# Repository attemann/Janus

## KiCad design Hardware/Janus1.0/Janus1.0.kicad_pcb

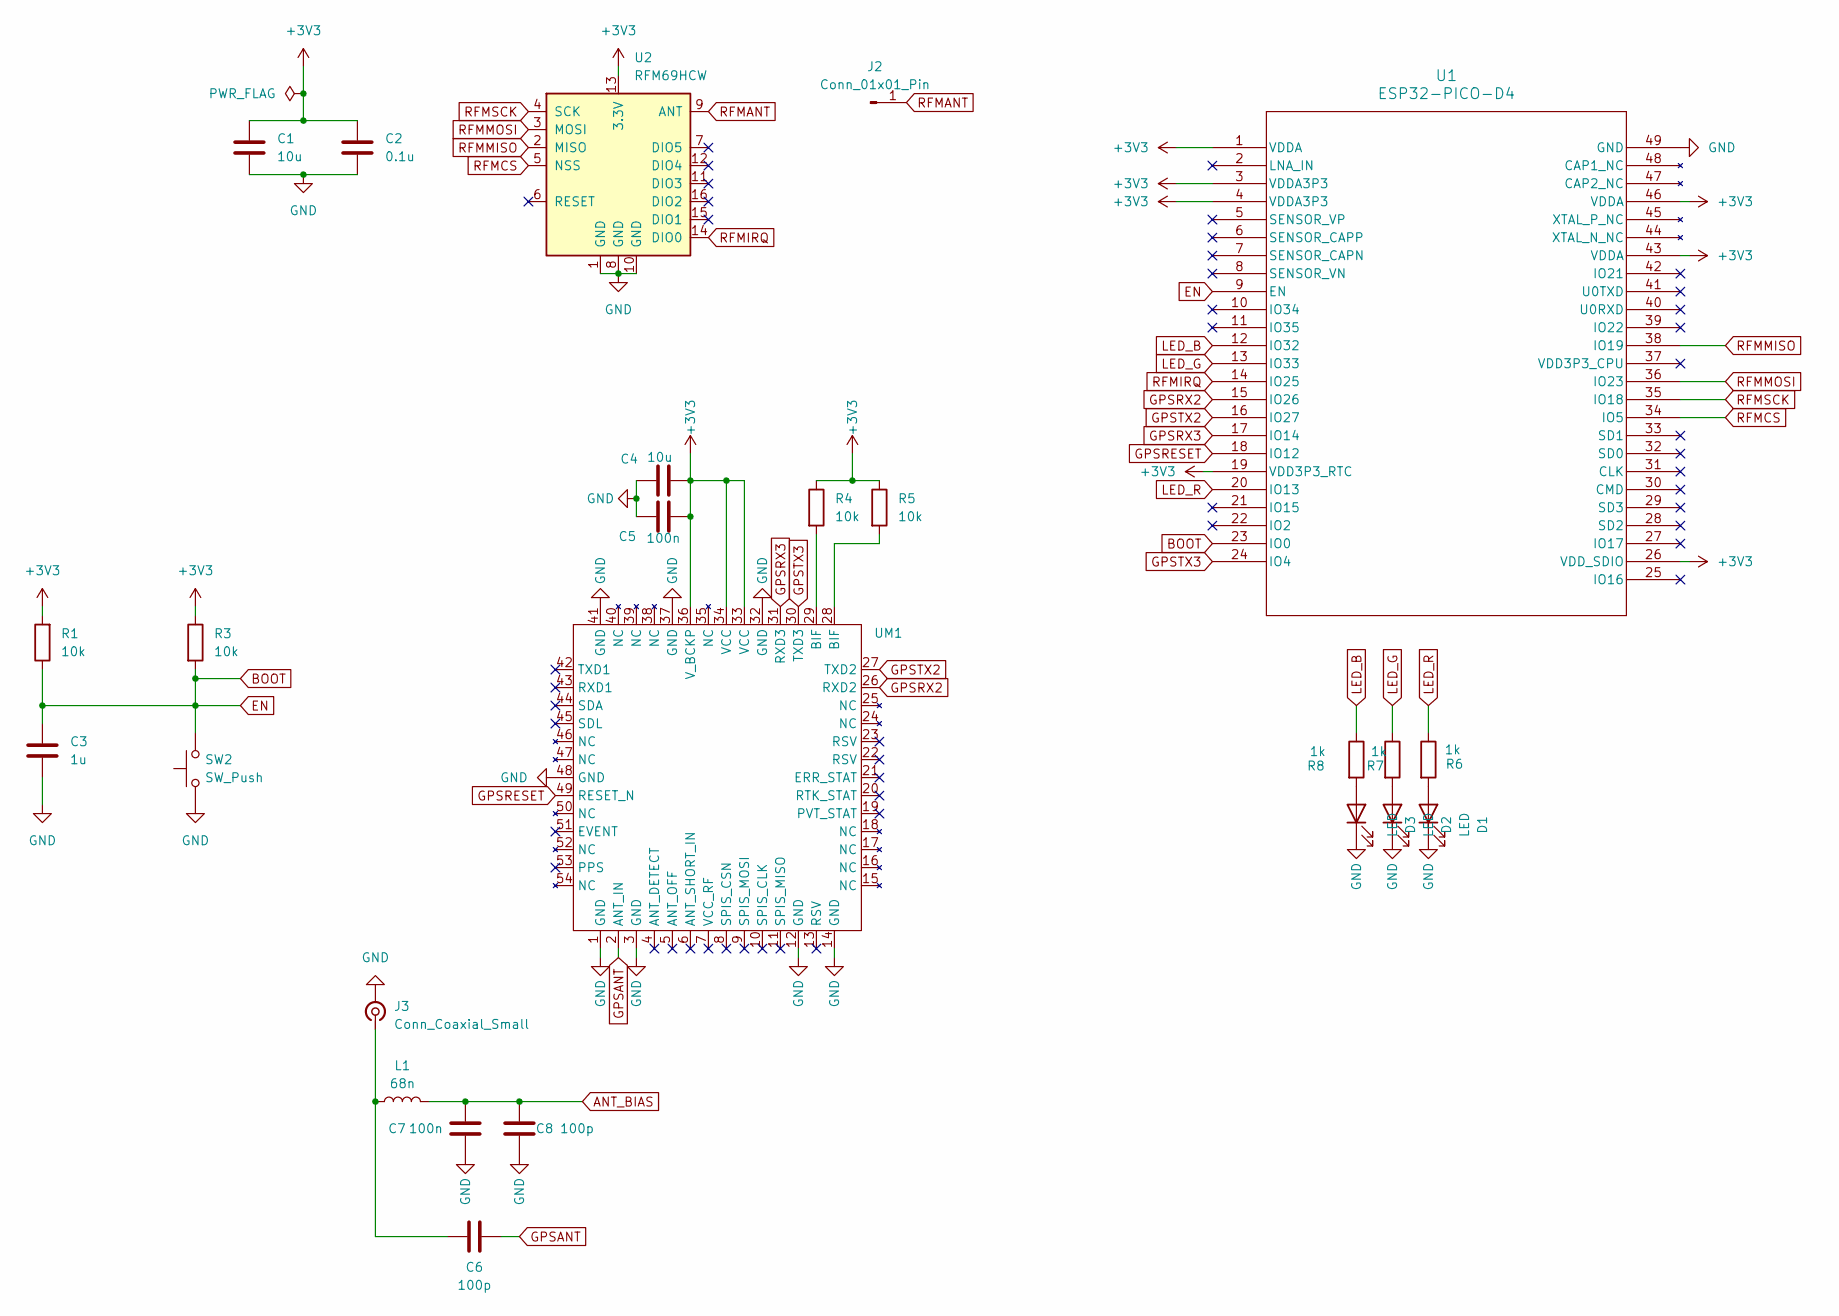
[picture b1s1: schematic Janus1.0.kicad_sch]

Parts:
C1, C4: 10u; C_0201_0603Metric
C2: 0.1u; C_0201_0603Metric
C3: 1u; C_0201_0603Metric
C5, C7: 100n; C_0201_0603Metric
C6, C8: 100p; C_0201_0603Metric
D1, D2, D3: LED; LED_0603_1608Metric
J2: Conn_01x01_Pin; PinHeader_1x01_P2.54mm_Vertical
J3: Conn_Coaxial_Small; U.FL_Hirose_U.FL-R-SMT-1_Vertical
L1: 68n; L_0201_0603Metric
R1, R3, R4, R5: 10k; R_0201_0603Metric
R6, R7, R8: 1k; R_0201_0603Metric
SW2: SW_Push; SW_Push_1P1T_NO_CK_PTS125Sx43PSMTR
U1: ESP32-PICO-D4; ESP32-PICO-D4_EXP
U2: RFM69HCW; MOD_COM-13909
UM1: UM980

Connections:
+3V3: C1.1, C2.1, C4.1, C5.1, R1.2, R3.1, R4.1, R5.1, U1.1 (VDDA), U1.3 (VDDA3P3), U1.4 (VDDA3P3), U1.19 (VDD3P3_RTC), U1.26 (VDD_SDIO), U1.43 (VDDA), U1.46 (VDDA), U2.13 (3.3V), UM1.33 (VCC), UM1.34 (VCC), UM1.36 (V_BCKP)
ANT_BIAS: C7.2, C8.2, L1.2
BOOT: C3.1, R1.1, R3.2, SW2.2, U1.9 (EN), U1.23 (IO0)
GND: C1.2, C2.2, C3.2, C4.2, C5.2, C7.1, C8.1, D1.1 (K), D2.1 (K), D3.1 (K), J3.2 (Ext), SW2.1, U1.49 (GND), U2.1 (GND), U2.8 (GND), U2.10 (GND), UM1.1 (GND), UM1.3 (GND), UM1.12 (GND), UM1.14 (GND), UM1.32 (GND), UM1.37 (GND), UM1.41 (GND), UM1.48 (GND)
GPSANT: C6.2, UM1.2 (ANT_IN)
GPSRESET: U1.18 (IO12), UM1.49 (RESET_N)
GPSRX2: U1.15 (IO26), UM1.26 (RXD2)
GPSRX3: U1.17 (IO14), UM1.31 (RXD3)
GPSTX2: U1.16 (IO27), UM1.27 (TXD2)
GPSTX3: U1.24 (IO4), UM1.30 (TXD3)
LED_B: R8.1, U1.12 (IO32)
LED_G: R7.1, U1.13 (IO33)
LED_R: R6.1, U1.20 (IO13)
unnamed: D1.2 (A), R6.2
unnamed: D2.2 (A), R7.2
unnamed: D3.2 (A), R8.2
unnamed: C6.1, J3.1 (In), L1.1
unnamed: R4.2, UM1.29 (BIF)
unnamed: R5.2, UM1.28 (BIF)
RFMANT: J2.1, U2.9 (ANT)
RFMCS: U1.34 (IO5), U2.5 (NSS)
RFMIRQ: U1.14 (IO25), U2.14 (DIO0)
RFMMISO: U1.38 (IO19), U2.2 (MISO)
RFMMOSI: U1.36 (IO23), U2.3 (MOSI)
RFMSCK: U1.35 (IO18), U2.4 (SCK)

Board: 4 copper layers, 25 parts (0 on the bottom side), 25 nets, no tracks yet.

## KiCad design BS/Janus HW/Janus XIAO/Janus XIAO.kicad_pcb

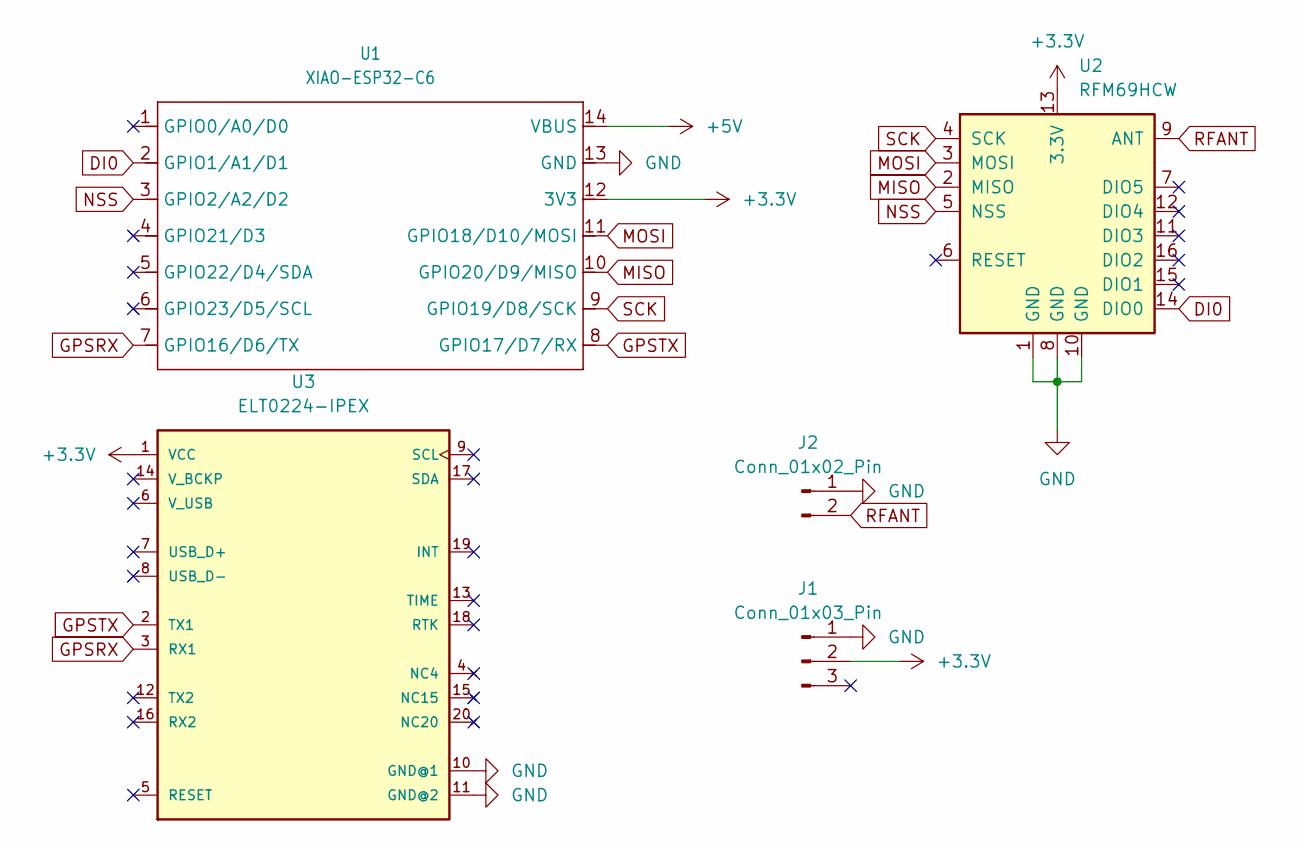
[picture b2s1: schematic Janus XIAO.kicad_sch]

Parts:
J1: Conn_01x03_Pin; PinHeader_1x03_P2.54mm_Vertical
J2: Conn_01x02_Pin; PinHeader_1x02_P2.54mm_Vertical
U1: XIAO-ESP32-C6; MCU_Seeed_ESP32C6 joe
U2: RFM69HCW; HOPERF_RFM9XW_SMD
U3: ELT0224-IPEX

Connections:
+3.3V: J1.2, U1.12 (3V3), U2.13 (3.3V), U3.1 (VCC)
+5V: U1.14 (VBUS)
DI0: U1.2 (GPIO1/A1/D1), U2.14 (DIO0)
GND: J1.1, J2.1, U1.13 (GND), U2.1 (GND), U2.8 (GND), U2.10 (GND), U3.10 (GND@1), U3.11 (GND@2)
GPSRX: U1.7 (GPIO16/D6/TX), U3.3 (RX1)
GPSTX: U1.8 (GPIO17/D7/RX), U3.2 (TX1)
MISO: U1.10 (GPIO20/D9/MISO), U2.2 (MISO)
MOSI: U1.11 (GPIO18/D10/MOSI), U2.3 (MOSI)
NSS: U1.3 (GPIO2/A2/D2), U2.5 (NSS)
RFANT: J2.2, U2.9 (ANT)
SCK: U1.9 (GPIO19/D8/SCK), U2.4 (SCK)

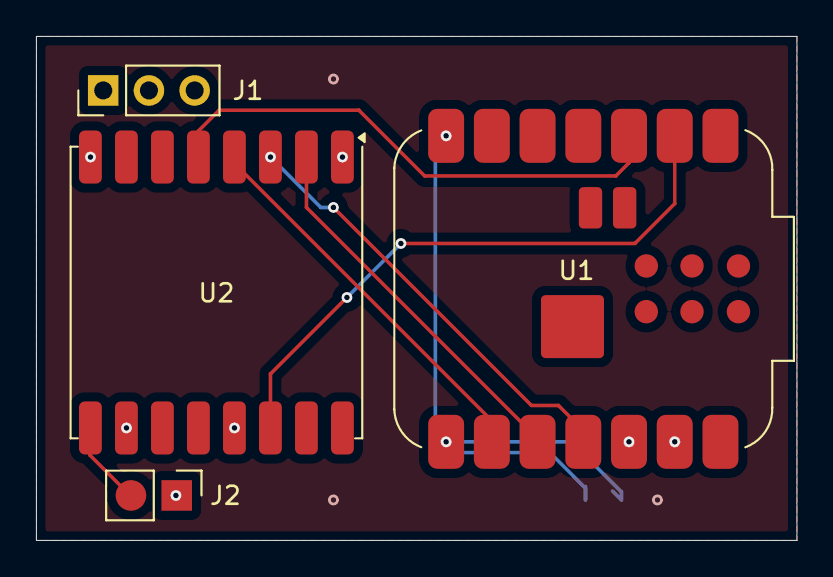
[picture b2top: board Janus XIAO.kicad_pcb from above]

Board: 4 copper layers, 42.2 x 28.0 mm, 5 parts (1 on the bottom side), 10 nets.

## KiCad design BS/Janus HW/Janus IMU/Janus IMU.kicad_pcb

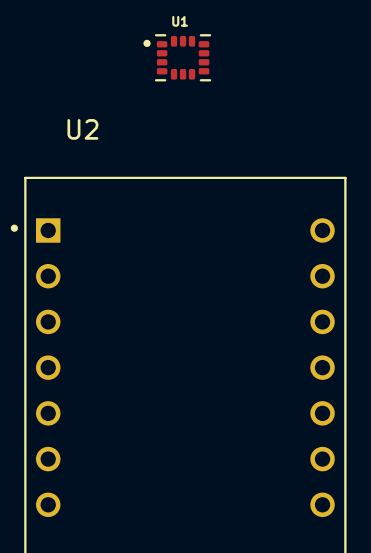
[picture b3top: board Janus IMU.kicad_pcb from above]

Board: 2 copper layers, 3 parts (1 on the bottom side), 3 nets, no tracks yet.

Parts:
U1: ICM-42688-P; PQFN50P300X250X97-14N
U2: XIAO ESP32-C6; MODULE_113991054
U4: RFM69HCW; HOPERF_RFM9XW_SMD

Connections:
+3.3V: U1.8 (VDD), U2.12 (VCC_3V3), U4.13 (3.3V)
GND: U1.6 (GND), U2.13 (GND), U4.1 (GND), U4.8 (GND), U4.10 (GND)
SCK: U4.2 (MISO), U4.3 (MOSI), U4.4 (SCK), U4.5 (NSS), U4.14 (DIO0)

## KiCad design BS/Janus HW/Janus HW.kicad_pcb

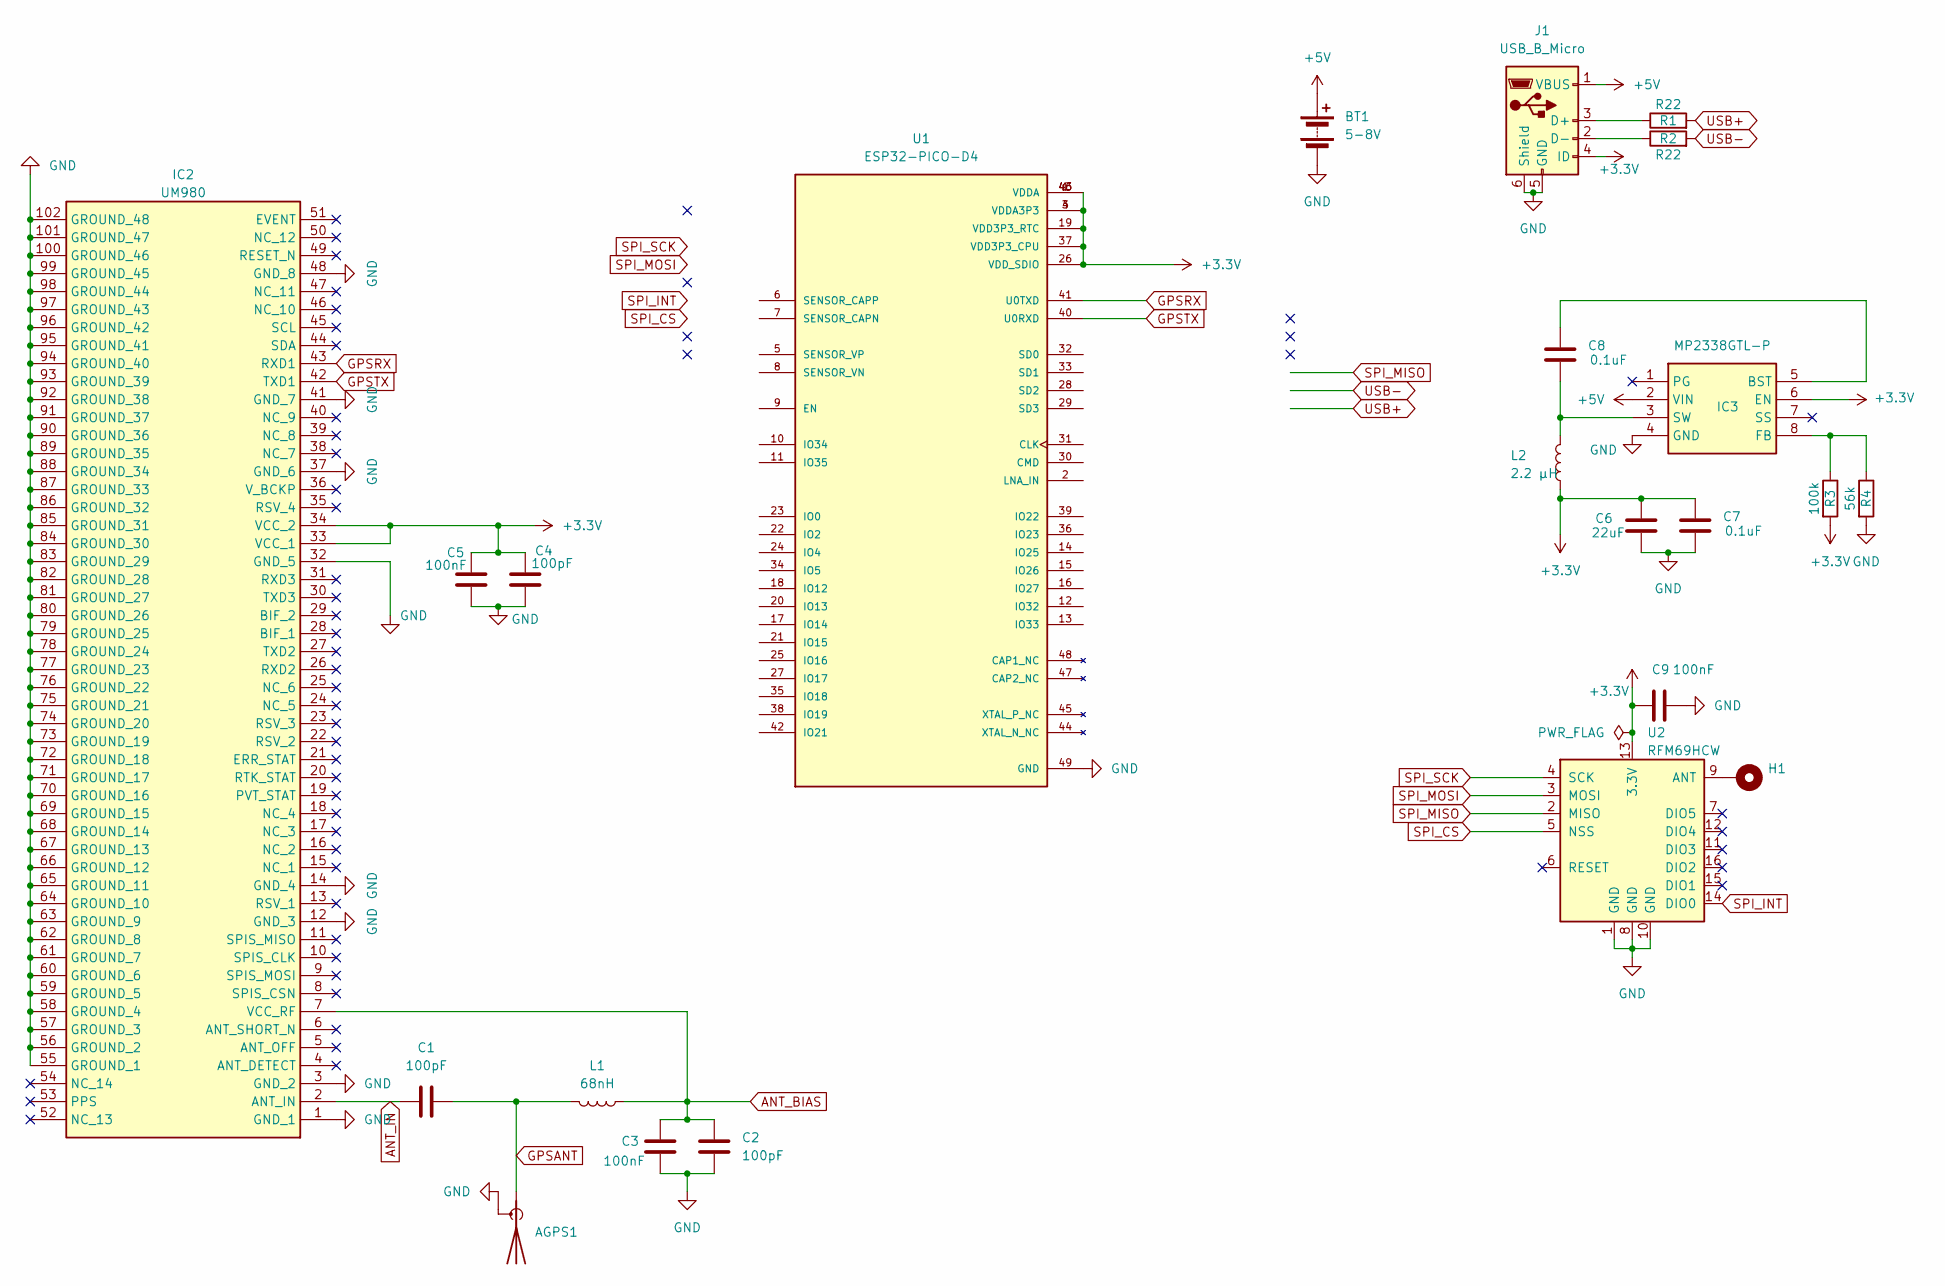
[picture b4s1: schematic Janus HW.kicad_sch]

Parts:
AGPS1: Antenna_Shield; U.FL_Molex_MCRF_73412-0110_Vertical
BT1: 5-8V
C1, C2, C4: 100pF; C_0201_0603Metric_Pad0.64x0.40mm_HandSolder
C3, C5, C9: 100nF; C_0201_0603Metric_Pad0.64x0.40mm_HandSolder
C6: 22uF; C_0201_0603Metric_Pad0.64x0.40mm_HandSolder
C7, C8: 0.1uF; C_0201_0603Metric_Pad0.64x0.40mm_HandSolder
H1: MountingHole_Pad; PinHeader_1x01_P1.27mm_Vertical
IC2: UM980; Manufacturer_Part_Number UM980
IC3: MP2338GTL-P; SOTFL50P160X60-8N; Manufacturer_Part_Number MP2338GTL-P; Mouser Part Number 946-MP2338GTL-P
J1: USB_B_Micro; USB_Micro-B_Amphenol_10118194-0001LF_Horizontal
L1: 68nH; L_0201_0603Metric
L2: 2.2 µH; L_0805_2012Metric
R1, R2: R22; R_0201_0603Metric_Pad0.64x0.40mm_HandSolder
R3: 100k; R_0201_0603Metric_Pad0.64x0.40mm_HandSolder
R4: 56k; R_0201_0603Metric_Pad0.64x0.40mm_HandSolder
U1: ESP32-PICO-D4; QFN-48-1EP_6x6mm_P0.4mm_EP4.3x4.3mm_ThermalVias; PARTREV v1.9; DigiKey_Part_Number 1904-1029-2-ND
U2: RFM69HCW; HOPERF_RFM9XW_THT_ikke_through

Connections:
+3.3V: C4.2, C5.2, C6.2, C7.2, C9.2, IC2.33 (VCC_1), IC2.34 (VCC_2), IC3.6 (EN), J1.4 (ID), L2.1, R3.2, U1.1 (VDDA), U1.3 (VDDA3P3), U1.4 (VDDA3P3), U1.19 (VDD3P3_RTC), U1.26 (VDD_SDIO), U1.37 (VDD3P3_CPU), U1.43 (VDDA), U1.46 (VDDA), U2.13 (3.3V)
+5V: BT1.1 (+), IC3.2 (VIN), J1.1 (VBUS)
ANT_BIAS: C2.2, C3.2, IC2.7 (VCC_RF), L1.1
ANT_IN: C1.1, IC2.2 (ANT_IN)
GND: AGPS1.2 (Shield), BT1.2 (-), C2.1, C3.1, C4.1, C5.1, C6.1, C7.1, C9.1, IC2.1 (GND_1), IC2.3 (GND_2), IC2.12 (GND_3), IC2.14 (GND_4), IC2.32 (GND_5), IC2.37 (GND_6), IC2.41 (GND_7), IC2.48 (GND_8), IC2.55 (GROUND_1), IC2.56 (GROUND_2), IC2.57 (GROUND_3), IC2.58 (GROUND_4), IC2.59 (GROUND_5), IC2.60 (GROUND_6), IC2.61 (GROUND_7), IC2.62 (GROUND_8), IC2.63 (GROUND_9), IC2.64 (GROUND_10), IC2.65 (GROUND_11), IC2.66 (GROUND_12), IC2.67 (GROUND_13), IC2.68 (GROUND_14), IC2.69 (GROUND_15), IC2.70 (GROUND_16), IC2.71 (GROUND_17), IC2.72 (GROUND_18), IC2.73 (GROUND_19), IC2.74 (GROUND_20), IC2.75 (GROUND_21), IC2.76 (GROUND_22), IC2.77 (GROUND_23), IC2.78 (GROUND_24), IC2.79 (GROUND_25), IC2.80 (GROUND_26), IC2.81 (GROUND_27), IC2.82 (GROUND_28), IC2.83 (GROUND_29), IC2.84 (GROUND_30), IC2.85 (GROUND_31), IC2.86 (GROUND_32), IC2.87 (GROUND_33), IC2.88 (GROUND_34), IC2.89 (GROUND_35), IC2.90 (GROUND_36), IC2.91 (GROUND_37), IC2.92 (GROUND_38), IC2.93 (GROUND_39), IC2.94 (GROUND_40), IC2.95 (GROUND_41), IC2.96 (GROUND_42), IC2.97 (GROUND_43), IC2.98 (GROUND_44), IC2.99 (GROUND_45), IC2.100 (GROUND_46), IC2.101 (GROUND_47), IC2.102 (GROUND_48), IC3.4 (GND), J1.5 (GND), J1.6 (Shield), R4.2, U1.49 (GND), U2.1 (GND), U2.8 (GND), U2.10 (GND)
GPSANT: AGPS1.1 (A), C1.2, L1.2
GPSRX: IC2.43 (RXD1), U1.41 (U0TXD)
GPSTX: IC2.42 (TXD1), U1.40 (U0RXD)
unnamed: C8.2, IC3.5 (BST)
unnamed: IC3.8 (FB), R3.1, R4.1
unnamed: C8.1, IC3.3 (SW), L2.2
unnamed: J1.3 (D+), R1.1
unnamed: J1.2 (D-), R2.1
unnamed: H1.1, U2.9 (ANT)
SPI_CS: U2.5 (NSS)
SPI_INT: U2.14 (DIO0)
SPI_MISO: U2.2 (MISO)
SPI_MOSI: U2.3 (MOSI)
SPI_SCK: U2.4 (SCK)
USB+: R1.2
USB-: R2.2

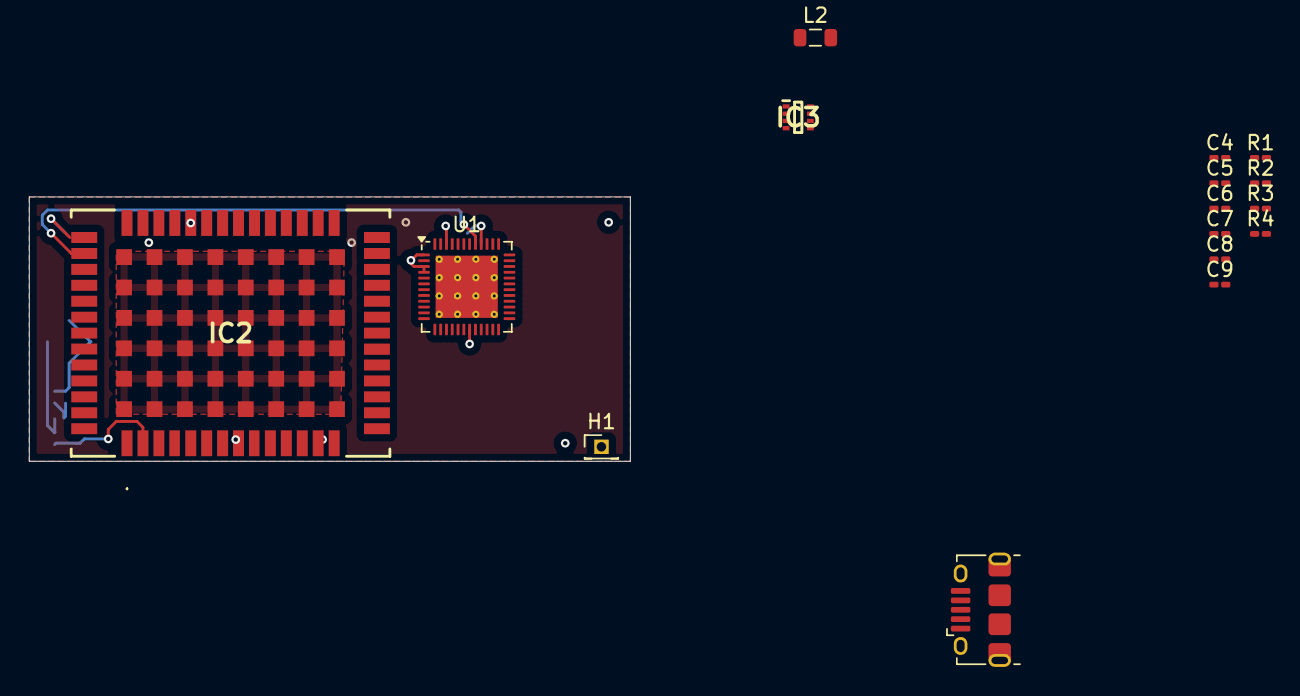
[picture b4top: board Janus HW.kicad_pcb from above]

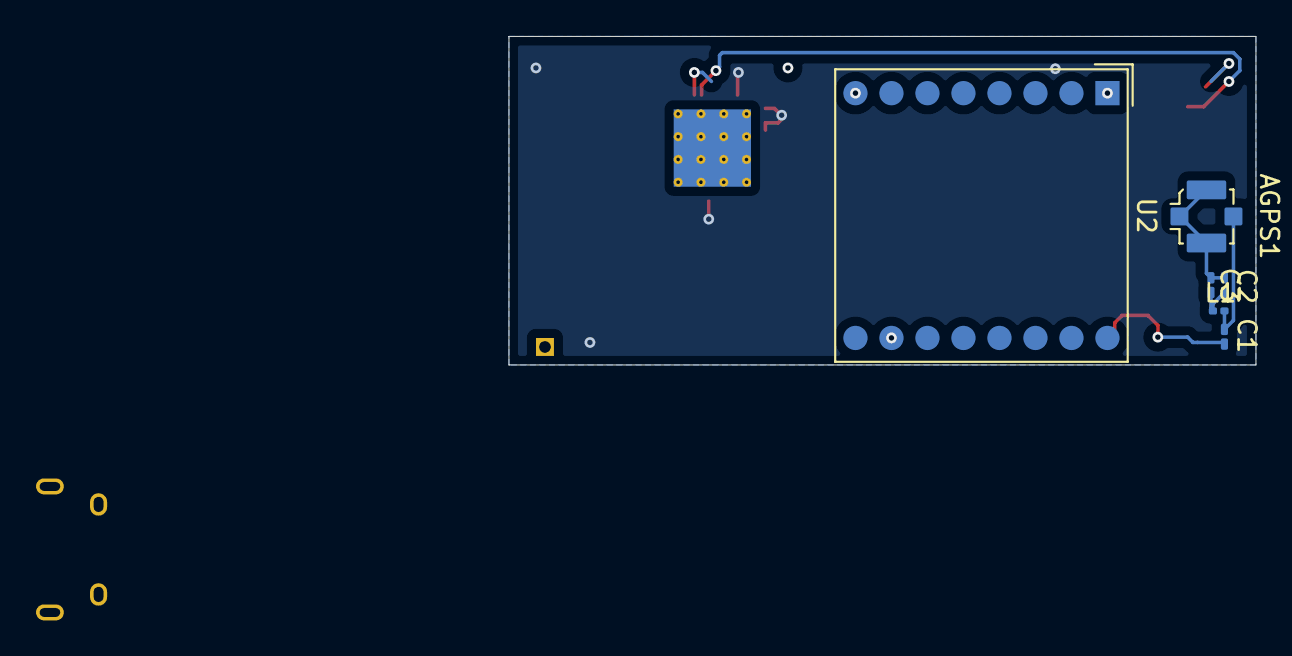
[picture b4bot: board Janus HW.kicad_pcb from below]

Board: 4 copper layers, 41.5 x 18.2 mm, 22 parts (6 on the bottom side), 14 nets.

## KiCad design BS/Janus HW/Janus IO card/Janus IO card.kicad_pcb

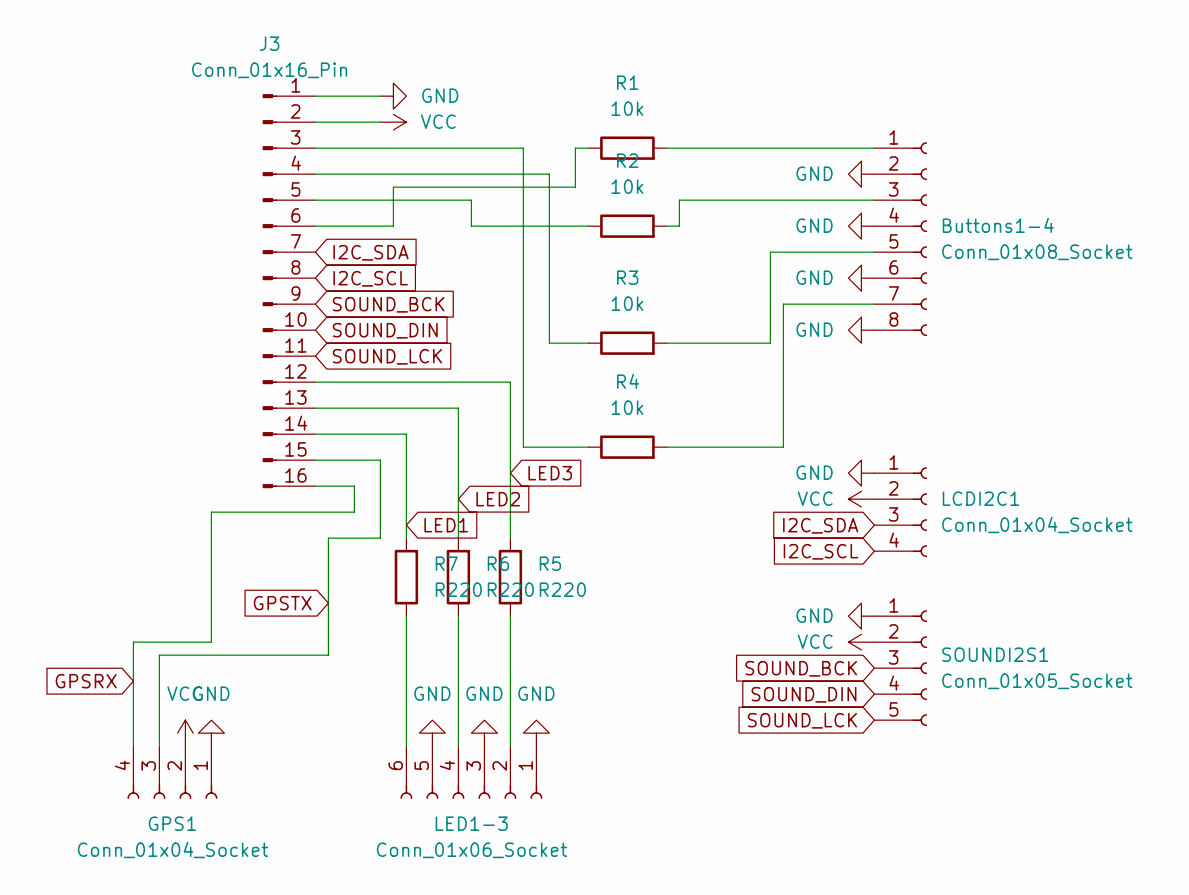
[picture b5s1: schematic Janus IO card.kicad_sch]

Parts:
Buttons1-4: Conn_01x08_Socket; JST_ZH_B8B-ZR_1x08_P1.50mm_Vertical
GPS1: Conn_01x04_Socket; JST_ZH_B4B-ZR_1x04_P1.50mm_Vertical
J3: Conn_01x16_Pin; TE_1-84952-6_1x16-1MP_P1.0mm_Horizontal
LCDI2C1: Conn_01x04_Socket; JST_ZH_B4B-ZR_1x04_P1.50mm_Vertical
LED1-3: Conn_01x06_Socket; JST_ZH_B6B-ZR_1x06_P1.50mm_Vertical
R1, R2, R3, R4: 10k; R_0805_2012Metric
R5, R6, R7: R220; R_0805_2012Metric
SOUNDI2S1: Conn_01x05_Socket; JST_ZH_B5B-ZR_1x05_P1.50mm_Vertical

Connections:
GND: Buttons1-4.2, Buttons1-4.4, Buttons1-4.6, Buttons1-4.8, GPS1.1, J3.1, LCDI2C1.1, LED1-3.1, LED1-3.3, LED1-3.5, SOUNDI2S1.1
GPSRX: GPS1.4, J3.16
GPSTX: GPS1.3, J3.15
I2C_SCL: J3.8, LCDI2C1.4
I2C_SDA: J3.7, LCDI2C1.3
LED1: J3.14, R7.2
LED2: J3.13, R6.2
LED3: J3.12, R5.2
unnamed: Buttons1-4.1, R1.2
unnamed: Buttons1-4.3, R2.2
unnamed: Buttons1-4.5, R3.2
unnamed: Buttons1-4.7, R4.2
unnamed: J3.3, R4.1
unnamed: J3.4, R3.1
unnamed: J3.5, R2.1
unnamed: J3.6, R1.1
unnamed: LED1-3.2, R5.1
unnamed: LED1-3.4, R6.1
unnamed: LED1-3.6, R7.1
SOUND_BCK: J3.9, SOUNDI2S1.3
SOUND_DIN: J3.10, SOUNDI2S1.4
SOUND_LCK: J3.11, SOUNDI2S1.5
VCC: GPS1.2, J3.2, LCDI2C1.2, SOUNDI2S1.2

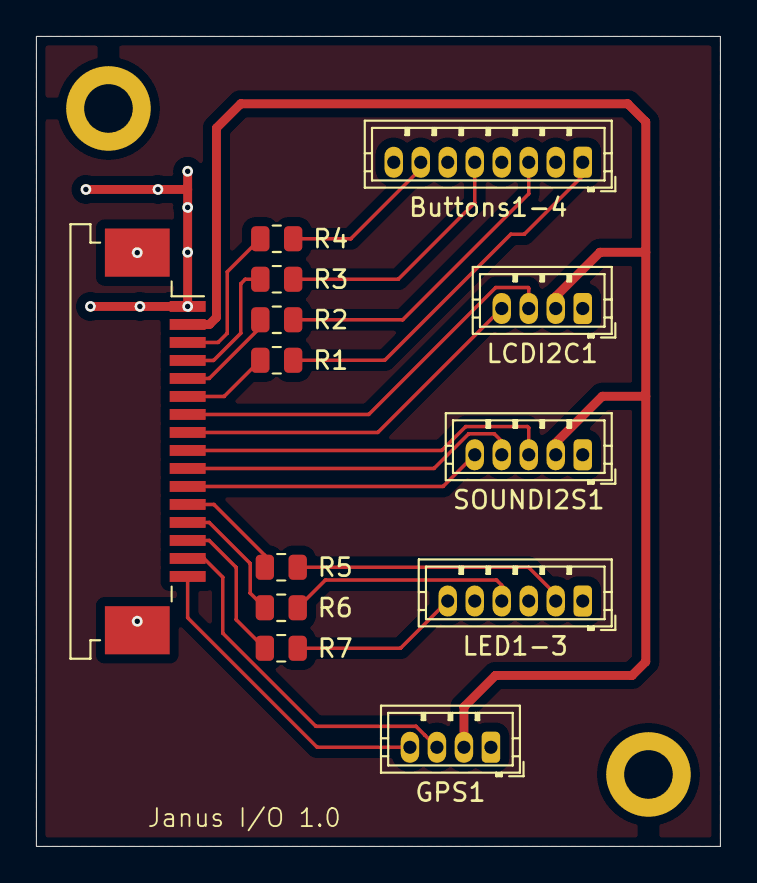
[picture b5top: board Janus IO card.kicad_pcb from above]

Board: 2 copper layers, 38.0 x 45.0 mm, 13 parts (0 on the bottom side), 23 nets.

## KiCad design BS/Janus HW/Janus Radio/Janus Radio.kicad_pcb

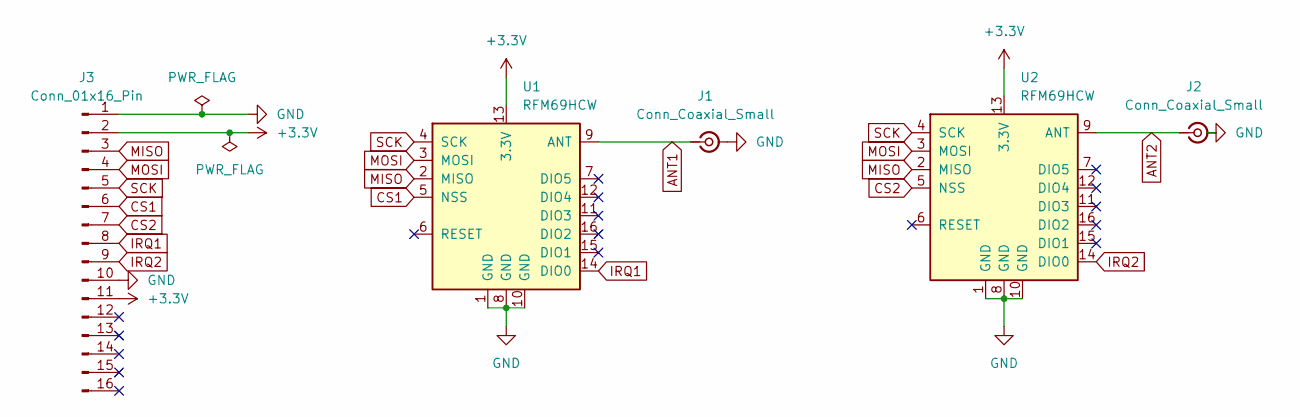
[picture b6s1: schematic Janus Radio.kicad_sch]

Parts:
J1, J2: Conn_Coaxial_Small; U.FL_Hirose_U.FL-R-SMT-1_Vertical
J3: Conn_01x16_Pin; TE_1-84952-6_1x16-1MP_P1.0mm_Horizontal
U1, U2: RFM69HCW; HOPERF_RFM9XW_SMD

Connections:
+3.3V: J3.2, J3.11, U1.13 (3.3V), U2.13 (3.3V)
ANT1: J1.1 (In), U1.9 (ANT)
ANT2: J2.1 (In), U2.9 (ANT)
CS1: J3.6, U1.5 (NSS)
CS2: J3.7, U2.5 (NSS)
GND: J1.2 (Ext), J2.2 (Ext), J3.1, J3.10, U1.1 (GND), U1.8 (GND), U1.10 (GND), U2.1 (GND), U2.8 (GND), U2.10 (GND)
IRQ1: J3.8, U1.14 (DIO0)
IRQ2: J3.9, U2.14 (DIO0)
MISO: J3.3, U1.2 (MISO), U2.2 (MISO)
MOSI: J3.4, U1.3 (MOSI), U2.3 (MOSI)
SCK: J3.5, U1.4 (SCK), U2.4 (SCK)

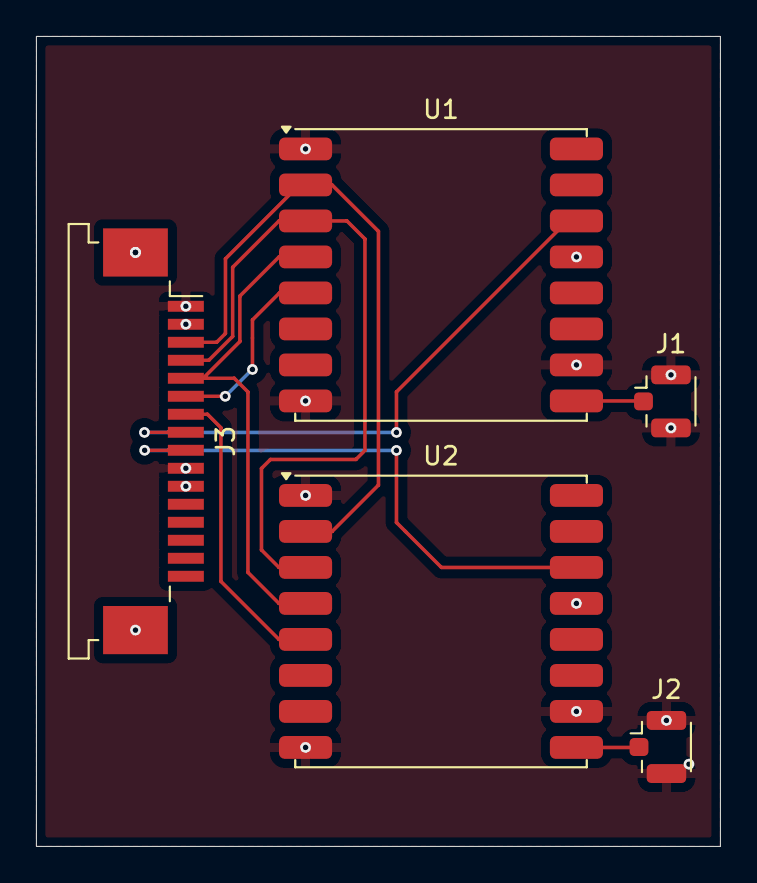
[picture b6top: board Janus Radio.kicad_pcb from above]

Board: 4 copper layers, 38.0 x 45.0 mm, 5 parts (0 on the bottom side), 11 nets.

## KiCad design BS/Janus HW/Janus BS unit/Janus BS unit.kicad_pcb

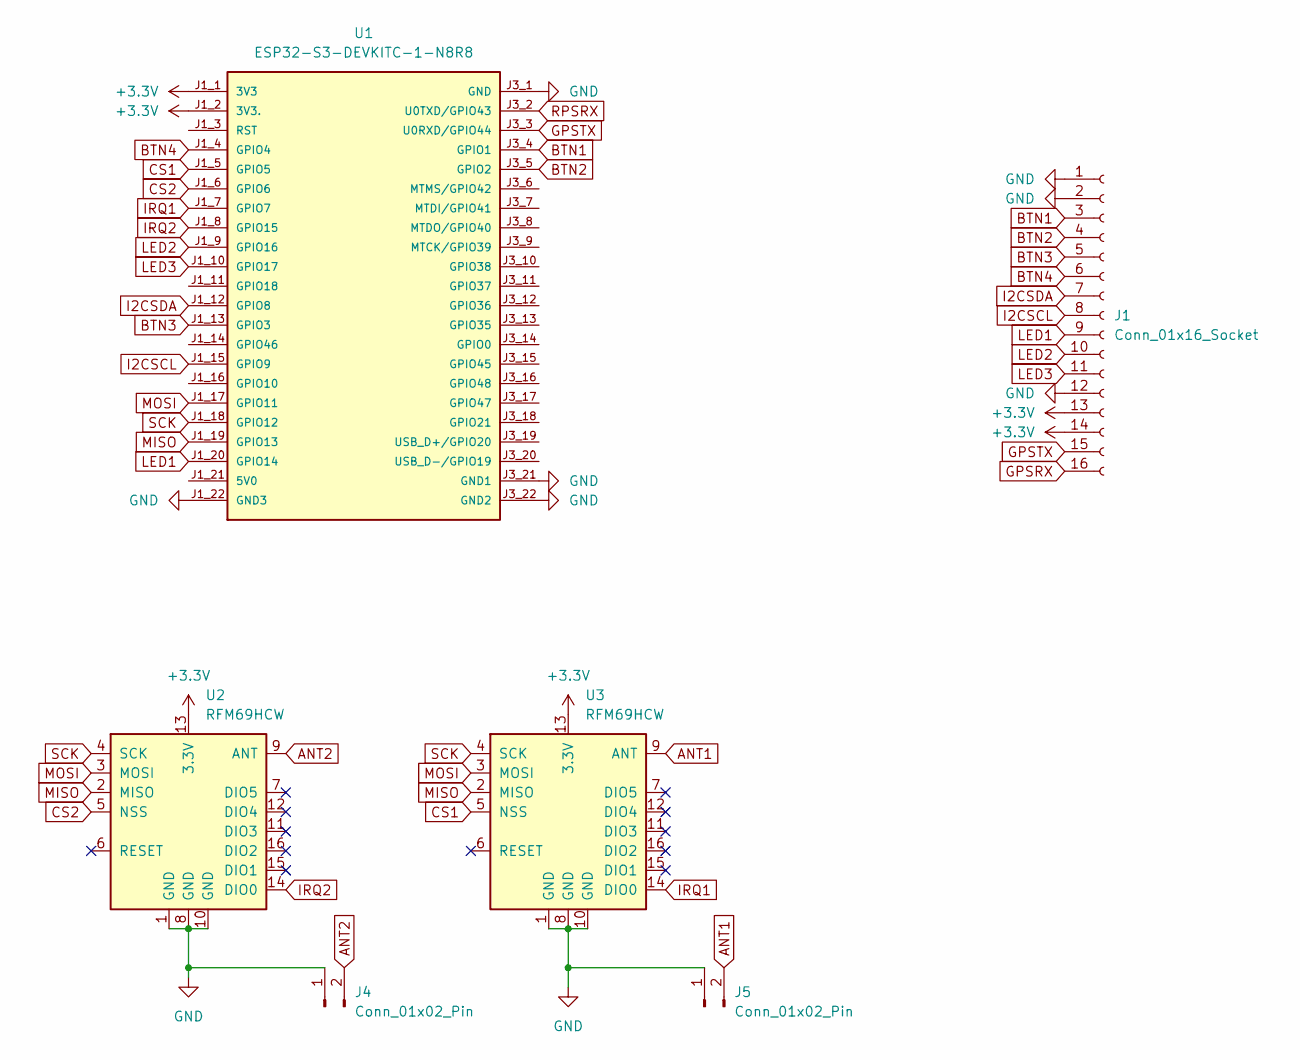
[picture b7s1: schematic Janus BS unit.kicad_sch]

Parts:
J1: Conn_01x16_Socket; PinSocket_1x16_P2.54mm_Vertical
J4, J5: Conn_01x02_Pin; PinHeader_1x02_P2.54mm_Vertical
U1: ESP32-S3-DEVKITC-1-N8R8
U2, U3: RFM69HCW; HOPERF_RFM9XW_SMD

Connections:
+3.3V: J1.13, J1.14, U1.J1_1 (3V3), U1.J1_2 (3V3.), U2.13 (3.3V), U3.13 (3.3V)
ANT1: J5.2, U3.9 (ANT)
ANT2: J4.2, U2.9 (ANT)
BTN1: J1.3, U1.J3_4 (GPIO1)
BTN2: J1.4, U1.J3_5 (GPIO2)
BTN3: J1.5, U1.J1_13 (GPIO3)
BTN4: J1.6, U1.J1_4 (GPIO4)
CS1: U1.J1_5 (GPIO5), U3.5 (NSS)
CS2: U1.J1_6 (GPIO6), U2.5 (NSS)
GND: J1.1, J1.2, J1.12, J4.1, J5.1, U1.J1_22 (GND3), U1.J3_1 (GND), U1.J3_21 (GND1), U1.J3_22 (GND2), U2.1 (GND), U2.8 (GND), U2.10 (GND), U3.1 (GND), U3.8 (GND), U3.10 (GND)
GPSTX: J1.15, U1.J3_3 (U0RXD/GPIO44)
I2CSCL: J1.8, U1.J1_15 (GPIO9)
I2CSDA: J1.7, U1.J1_12 (GPIO8)
IRQ1: U1.J1_7 (GPIO7), U3.14 (DIO0)
IRQ2: U1.J1_8 (GPIO15), U2.14 (DIO0)
LED1: J1.9, U1.J1_20 (GPIO14)
LED2: J1.10, U1.J1_9 (GPIO16)
LED3: J1.11, U1.J1_10 (GPIO17)
MISO: U1.J1_19 (GPIO13), U2.2 (MISO), U3.2 (MISO)
MOSI: U1.J1_17 (GPIO11), U2.3 (MOSI), U3.3 (MOSI)
SCK: U1.J1_18 (GPIO12), U2.4 (SCK), U3.4 (SCK)

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
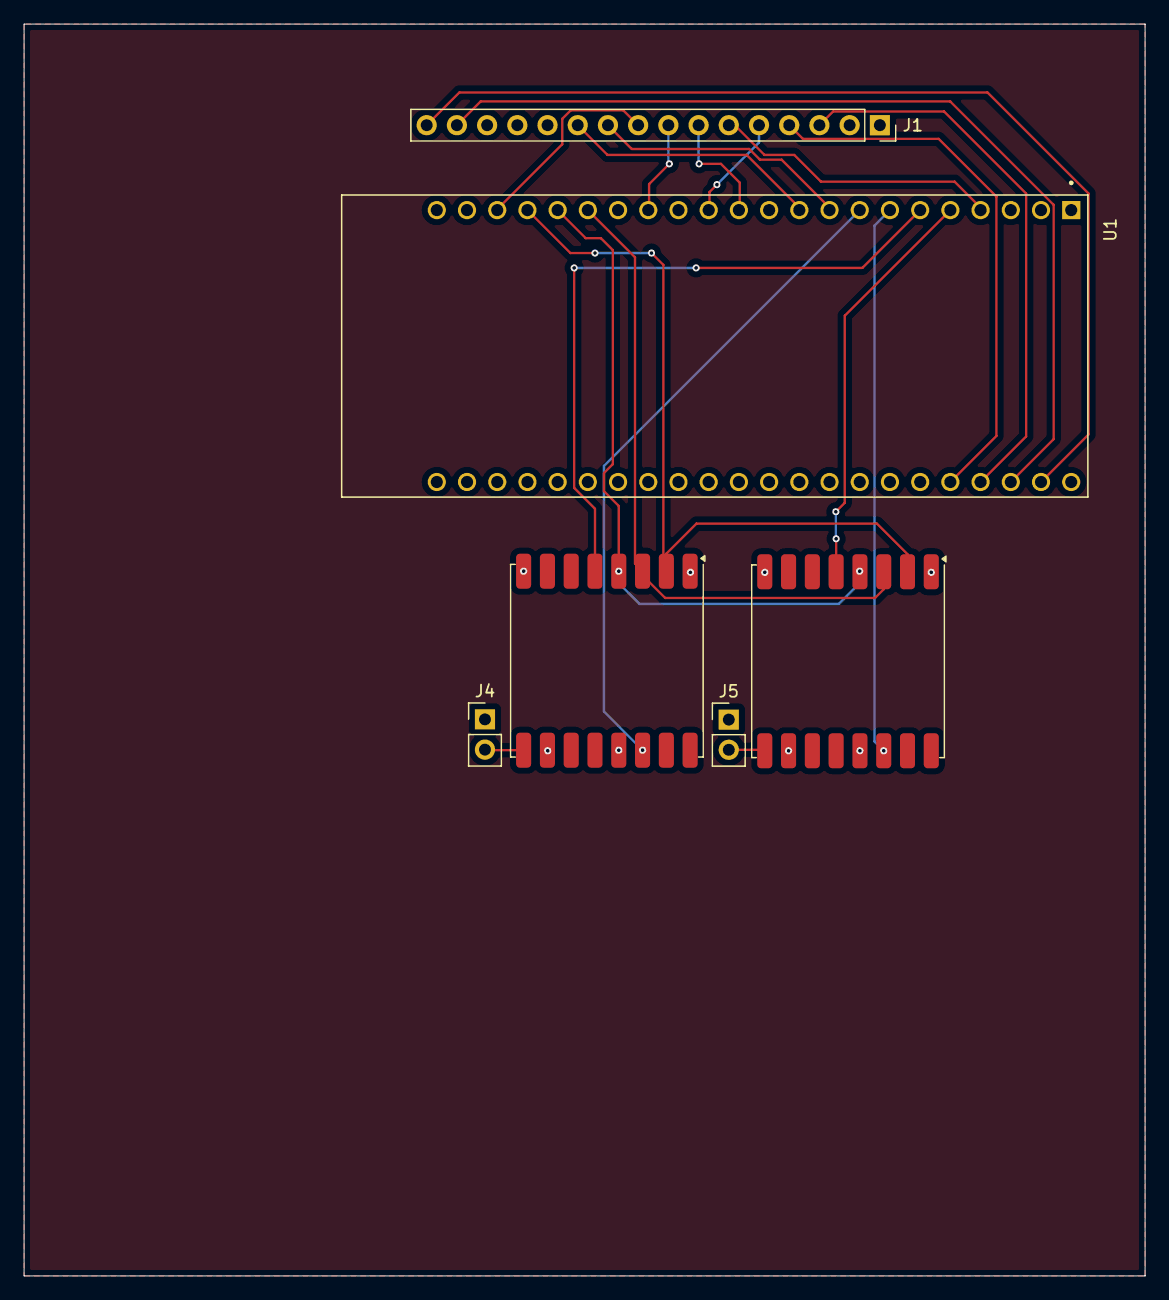
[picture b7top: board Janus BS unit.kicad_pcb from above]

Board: 4 copper layers, 94.2 x 105.2 mm, 6 parts (0 on the bottom side), 22 nets.

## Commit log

2025-05-24 Rydd opp etter .gitignore
2025-05-24 README.md
2025-05-26 Kicad hardware design
2025-05-27 Fiddling in Kicad
2025-06-30 A lot of stuff
2025-07-10 Status before swapping GNSS lib
2025-07-11 Using new UM980 lib
2025-07-13 RTCM output now works
2025-07-28 Understanding RFM69HCW boardcast
2025-08-01 RTCM transmission
2025-08-01 First classifying done
2025-08-02 LCDManager class
2025-08-02 GU classified
2025-08-03 Issues with large RTCMs
2025-08-04 DecimalSpeaker.h
2025-08-05 Sound, adding words
2025-08-05 Playing information and errors
2025-08-05 CD play messages working
2025-08-06 Fixed bug in RTCM segmenter
2025-08-07 RTCM class, logging
2025-08-07 Working on RTCM fragments
2025-08-07 Cleaning up debug code
2025-08-14 Struggling with radio
2025-08-15 Working on it...
2025-08-15 RFM bug was nullptr in init()
2025-08-18 Unified parsing in progress
2025-08-18 RTKBase and CD now compiles
2025-08-19 Macros
2025-08-21 Taskify Radio on RTKBase
2025-08-21 Enums, then GU
2025-08-22 detectUart fix
2025-08-30 RTCM transmission seems to work, in RTKBase
2025-09-01 Working....
2025-09-11 Moved away from tasks/queues
2025-09-12 Crash issues disappeared?!
2025-09-13 Woodstock
2025-09-14 RTCM transmit + receive works
2025-09-15 Works! gettin fix=2
2025-10-05 GU working
2025-10-08 GU and BASE now working: Got FixType=5
2025-10-09 New bullseye
